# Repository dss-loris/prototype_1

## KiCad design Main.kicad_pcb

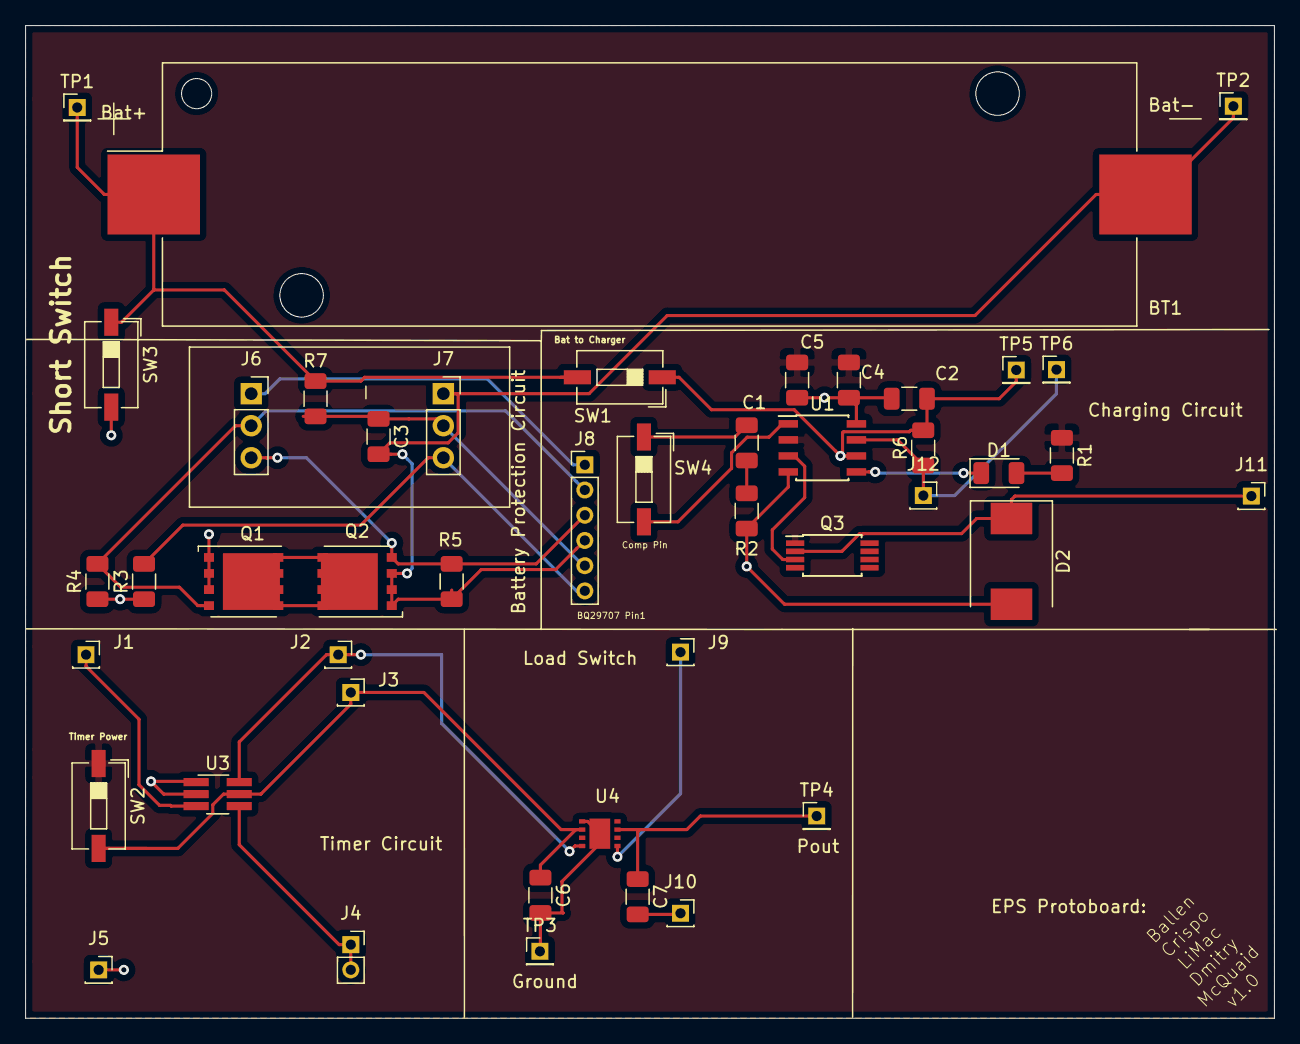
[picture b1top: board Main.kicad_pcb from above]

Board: 2 copper layers, 99.1 x 78.7 mm, 45 parts (0 on the bottom side), 25 nets.

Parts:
BT1: Cell1; BatteryHolder_Keystone_1042_1x18650
C1: 0.47u; C_1206_3216Metric
C2: 22u; C_1206_3216Metric
C3, C5, C6: 0.1u; C_1206_3216Metric
C4: 10u; C_1206_3216Metric
C7: 150u; C_1206_3216Metric
D1: LED; LED_1206_3216Metric
D2: B330; D_SMC
J1, J2, J3, J5, J9, J10, J11, J12: Conn_01x01_Female; PinSocket_1x01_P2.00mm_Vertical
J4: Conn_01x02_Female; PinSocket_1x02_P2.00mm_Vertical
J6, J7: Conn_01x03; PinSocket_1x03_P2.54mm_Vertical
J8: Conn_01x06; PinHeader_1x06_P2.00mm_Vertical
Q1, Q2: CSD17307Q5A; TDSON-8-1
Q3: Si6435ADQ; TSSOP-8_4.4x3mm_P0.65mm
R1: 2k; R_1206_3216Metric
R2, R3: 2.2k; R_1206_3216Metric
R4, R5: 5M; R_1206_3216Metric
R6: 59m; R_1206_3216Metric
R7: 330; R_1206_3216Metric
SW1, SW2, SW3, SW4: SW_Push; SW_DIP_SPSTx01_Slide_6.7x4.1mm_W6.73mm_P2.54mm_LowProfile_J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
TP1, TP2, TP3, TP4, TP5, TP6: TestPoint; PinHeader_1x01_P2.00mm_Vertical
U1: LTC4002ES8-4.2; SOIC-8_3.9x4.9mm_P1.27mm
U3: LTC6995-1; TSOT-23-6_HandSoldering
U4: TPS2557

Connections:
+5V: C4.1, C5.1, Q3.1, R1.1, SW2.1, U1.2
/BQ29707_P1: J6.1, J8.1
/BQ29707_P2: J6.2, J8.2, Q1.4, R4.2
/BQ29707_P3: J6.3, J8.3, Q2.4, R5.2
/BQ29707_P4: BT1.2, C3.2, J7.1, J8.4, Q2.1, Q2.2, Q2.3, R5.1, TP2.1
/BQ29707_P5: C3.1, J7.2, J8.5, R7.2
/BQ29707_P6: J7.3, J8.6, R3.2
BAT: BT1.1, R7.1, SW1.2, SW3.1, TP1.1
GNDD: C2.2, C4.2, C5.2, C6.2, C7.2, D2.2, J5.1, J10.1, Q1.1, Q1.2, Q1.3, R2.2, R3.1, R4.1, SW3.2, TP3.1, U1.4, U1.8, U3.1, U3.2, U4.1
unnamed: C1.1, SW4.1
unnamed: C1.2, R2.1
unnamed: C2.1, R6.2, SW1.1, TP5.1, U1.6
unnamed: C6.1, J3.1, SW2.2, U3.5, U4.2
unnamed: C7.1, TP4.1, U4.7
unnamed: D1.1, U1.5
unnamed: D1.2, R1.2
unnamed: D2.1, J11.1, Q3.2
unnamed: J1.1, U3.3
unnamed: J2.1, U3.6, U4.4
unnamed: J4.1, J4.2, U3.4
unnamed: J9.1, U4.5
unnamed: J12.1, R6.1, TP6.1, U1.7
unnamed: Q1.5, Q2.5
unnamed: Q3.3, U1.3
unnamed: SW4.2, U1.1

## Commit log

2019-04-28 moved solar cell current sensor and load switch to root sheet
2019-04-28 added schematic for Batt, BCR, and PDU
2019-04-29 added current sensing circuit and 5v/3.3v voltage monitoring
2019-05-13 Added libraries
    Addition of 555 & 4.2-5V Regulator libraries
2019-05-21 Imported 5V Regulator and 30 minute timer
    Added libraries to the working libraries in the main project. Also imported the 4.2-5VDC regulator and 30 minute timer schematics.
2019-05-24 changed msp430
2019-05-28 Added two more batteries for 4P configuration, added TI BQ297xx battery protection IC and PTC resettable fuse
2019-05-29 added system switch to negative terminal of battery pack. moved BDR and BCR to hierarchical sheets for improved readability
2019-05-31 Added more hierarchical sheets to improve readability, restructured the main schematic, and added ideal diode betewen BCR and BDR
2019-06-03 Added 5MOhm resistor across gatesource of power mosfet in battery cell protection schematic
2019-06-05 rearranged op amps
2019-06-10 added new timer circuit and changed deployment switch architecture
2019-06-13 updated MOSFET model in battery cell protection schematic. Refused PTC fuse due to uncertain behaviour under conformal coating and in vacuum.
2019-06-13 test commit
2019-06-17 started assigning footprints
2019-06-17 added more footprints
2019-06-18 need to add tps2557 footprint
2019-06-19 testing if opens properly
2019-06-19 started pcb
2019-06-19 finished traces
2019-06-21 allot a work
2019-06-21 still need breakout board for bq29707
2019-06-21 Finished, should be reviewed
2019-06-24 added edge cut layer
2019-06-24 reviewed footprints
2019-06-24 added final silk comments
2019-06-24 added changes mark wante
2019-06-24 changes for BOM
2019-06-24 regenerated gerbers
2019-07-02 changed transistor
